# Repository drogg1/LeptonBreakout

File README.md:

# LeptonBreakout
Eagle files for FLIR Lepton LWIR Camera Module Breakout Board

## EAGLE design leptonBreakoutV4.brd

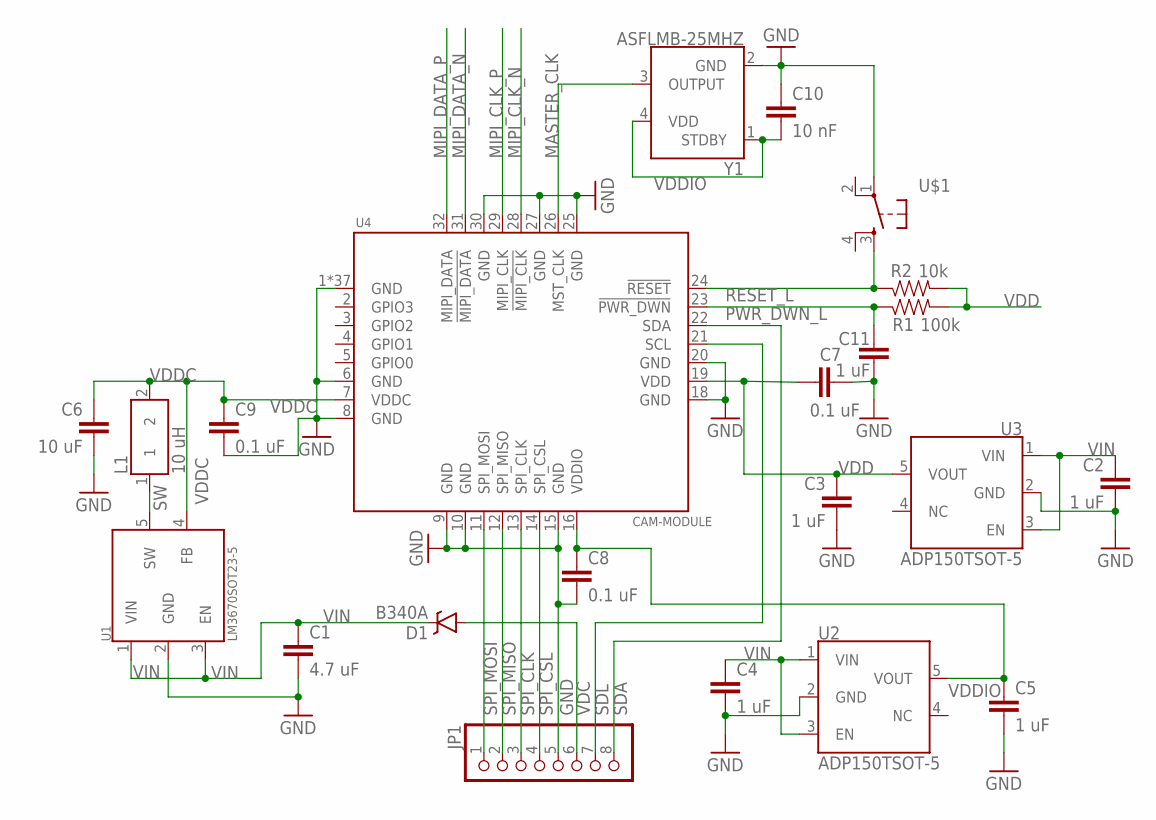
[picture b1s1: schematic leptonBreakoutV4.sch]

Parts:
C1: 4.7 uF; 0805
C2, C3, C4, C5, C11: 1 uF; 0805
C6: 10 uF; 0805
C7, C8, C9: 0.1 uF; 0805
C10: 10 nF; 0805
D1: B340A; SMA-DIODE
JP1: PINHD-1X8/90; 1X08/90
L1: 10 uH; SMD-INDUCTOR
R1: 100k; 0805
R2: 10k; 0805
U1: LM3670SOT23-5; SOT23-5
U2, U3: ADP150TSOT-5; SOT23-5
U4: CAM-MODULE; CAM-SOCKET
U$1: TACTILE-SWITCH-7914G; 7914G
Y1: ASFLMB-25MHZ; 5X3.2-CRYSTAL-OSC

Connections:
GND: C1.2, C2.2, C3.2, C4.2, C5.2, C6.2, C7.2, C8.2, C9.2, C10.1, C11.2, JP1.5, U1.2 (GND), U2.2 (GND), U3.2 (GND), U4.1 (GND), U4.6 (GND), U4.8 (GND), U4.9 (GND), U4.10 (GND), U4.15 (GND), U4.18 (GND), U4.20 (GND), U4.25 (GND), U4.27 (GND), U4.30 (GND), U4.P$1 (GND), U4.P$2 (GND), U4.P$3 (GND), U4.P$4 (GND), U4.P$5 (GND), U4.P$6 (GND), U4.P$7 (GND), U4.P$8 (GND), U4.P$9 (GND), U4.P$10 (GND), U4.P$11 (GND), U4.P$12 (GND), U4.P$13 (GND), U4.P$14 (GND), U4.P$15 (GND), U4.P$16 (GND), U4.P$17 (GND), U4.P$18 (GND), U4.P$19 (GND), U4.P$20 (GND), U4.P$21 (GND), U4.P$22 (GND), U4.P$23 (GND), U4.P$24 (GND), U4.P$25 (GND), U4.P$26 (GND), U4.P$27 (GND), U4.P$28 (GND), U4.P$29 (GND), U4.P$30 (GND), U4.P$31 (GND), U4.P$32 (GND), U4.P$33 (GND), U4.P$34 (GND), U4.P$35 (GND), U4.P$36 (GND), U$1.1, Y1.2 (GND)
MASTER_CLK: U4.26 (MST_CLK), Y1.3 (OUTPUT)
MIPI_CLK_N: U4.28 (!MIPI_CLK)
MIPI_CLK_P: U4.29 (MIPI_CLK)
MIPI_DATA_N: U4.31 (!MIPI_DATA)
MIPI_DATA_P: U4.32 (MIPI_DATA)
PWR_DWN_L: C11.1, R1.1, U4.23 (!PWR_DWN)
RESET_L: R2.1, U4.24 (!RESET), U$1.3
SDA: JP1.8, U4.22 (SDA)
SDL: JP1.7, U4.21 (SCL)
SPI_CLK: JP1.3, U4.13 (SPI_CLK)
SPI_CSL: JP1.4, U4.14 (SPI_CSL)
SPI_MISO: JP1.2, U4.12 (SPI_MISO)
SPI_MOSI: JP1.1, U4.11 (SPI_MOSI)
SW: L1.1, U1.5 (SW)
VDC: D1.A, JP1.6
VDD: C3.1, C7.1, R1.2, R2.2, U3.5 (VOUT), U4.19 (VDD)
VDDC: C6.1, C9.1, L1.2, U1.4 (FB), U4.7 (VDDC)
VDDIO: C5.1, C8.1, C10.2, U2.5 (VOUT), U4.16 (VDDIO), Y1.1 (STDBY), Y1.4 (VDD)
VIN: C1.1, C2.1, C4.1, D1.C, U1.1 (VIN), U1.3 (EN), U2.1 (VIN), U2.3 (EN), U3.1 (VIN), U3.3 (EN)

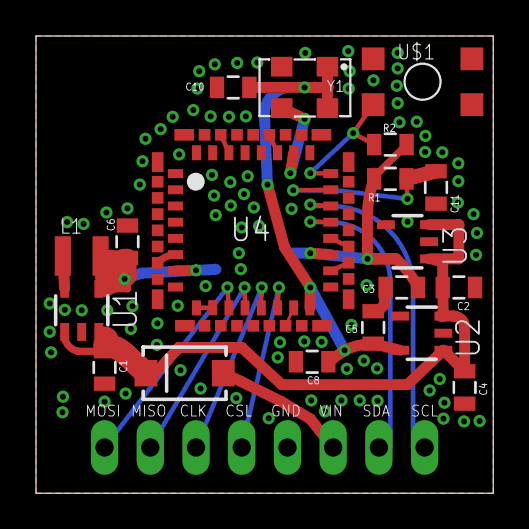
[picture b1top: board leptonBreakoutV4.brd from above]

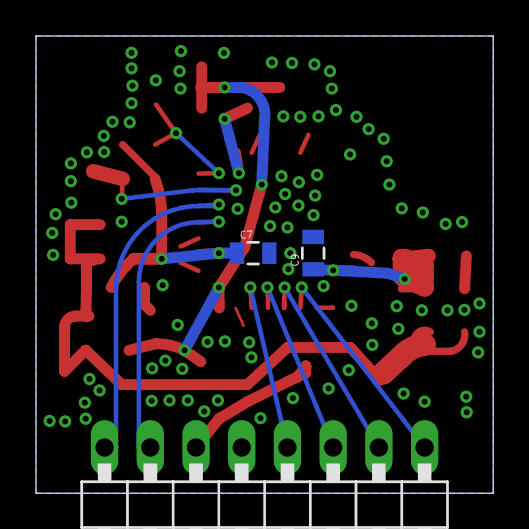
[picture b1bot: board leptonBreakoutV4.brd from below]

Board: 2 copper layers, 25.4 x 25.4 mm, 22 parts (3 on the bottom side), 16 nets.

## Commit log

2015-06-22 Initial Eagle files
2016-02-13 Latest version, smaller footprint, added reset button

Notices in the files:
parts and their libraries:
SparkFun-Capacitors: Licensing: Creative Commons ShareAlike 4.0 International - https://creativecommons.org/licenses/by-sa/4.0
